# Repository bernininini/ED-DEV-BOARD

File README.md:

# ED-DEV-BOARD
The Ed Dev Board is a custom dev board featuring a Qwiic port and powered by the ESP32-S3 WROOM 1. A custom PCB to provide an easy access and accessible dev board for prototyping and electronics projects that minimize the wiring.

*Qwiic is a type of connecting system that uses the I2C protocol, that only uses 4 pins (VCC, GND, SDA, SCL)

Reference: 
https://www.sparkfun.com/qwiic 

BOM:
| Reference                      | Qty | Value            | Part Name                     |
| ------------------------------ | --- | ---------------- | ----------------------------- |
| QWIIC1, QWIIC2, QWIIC3, QWIIC4 | 4   | port1            | Qwiic Port                    |
| R1, R2                         | 2   | 5.1k             | Resistor 0805                 |
| R3, R4, R5, R6                 | 4   | 10k              | Resistor 0805                 |
| SW1, SW2                       | 2   | SW\_Push         | Push Button 6mm               |
| U1                             | 1   | ESP32-S3-WROOM-1 | ESP32-S3-WROOM-1 Module       |
| U2                             | 1   | AMS1117-3.3      | Voltage Regulator AMS1117-3.3 |
| U3                             | 1   | \~               | USB-C Connector               |

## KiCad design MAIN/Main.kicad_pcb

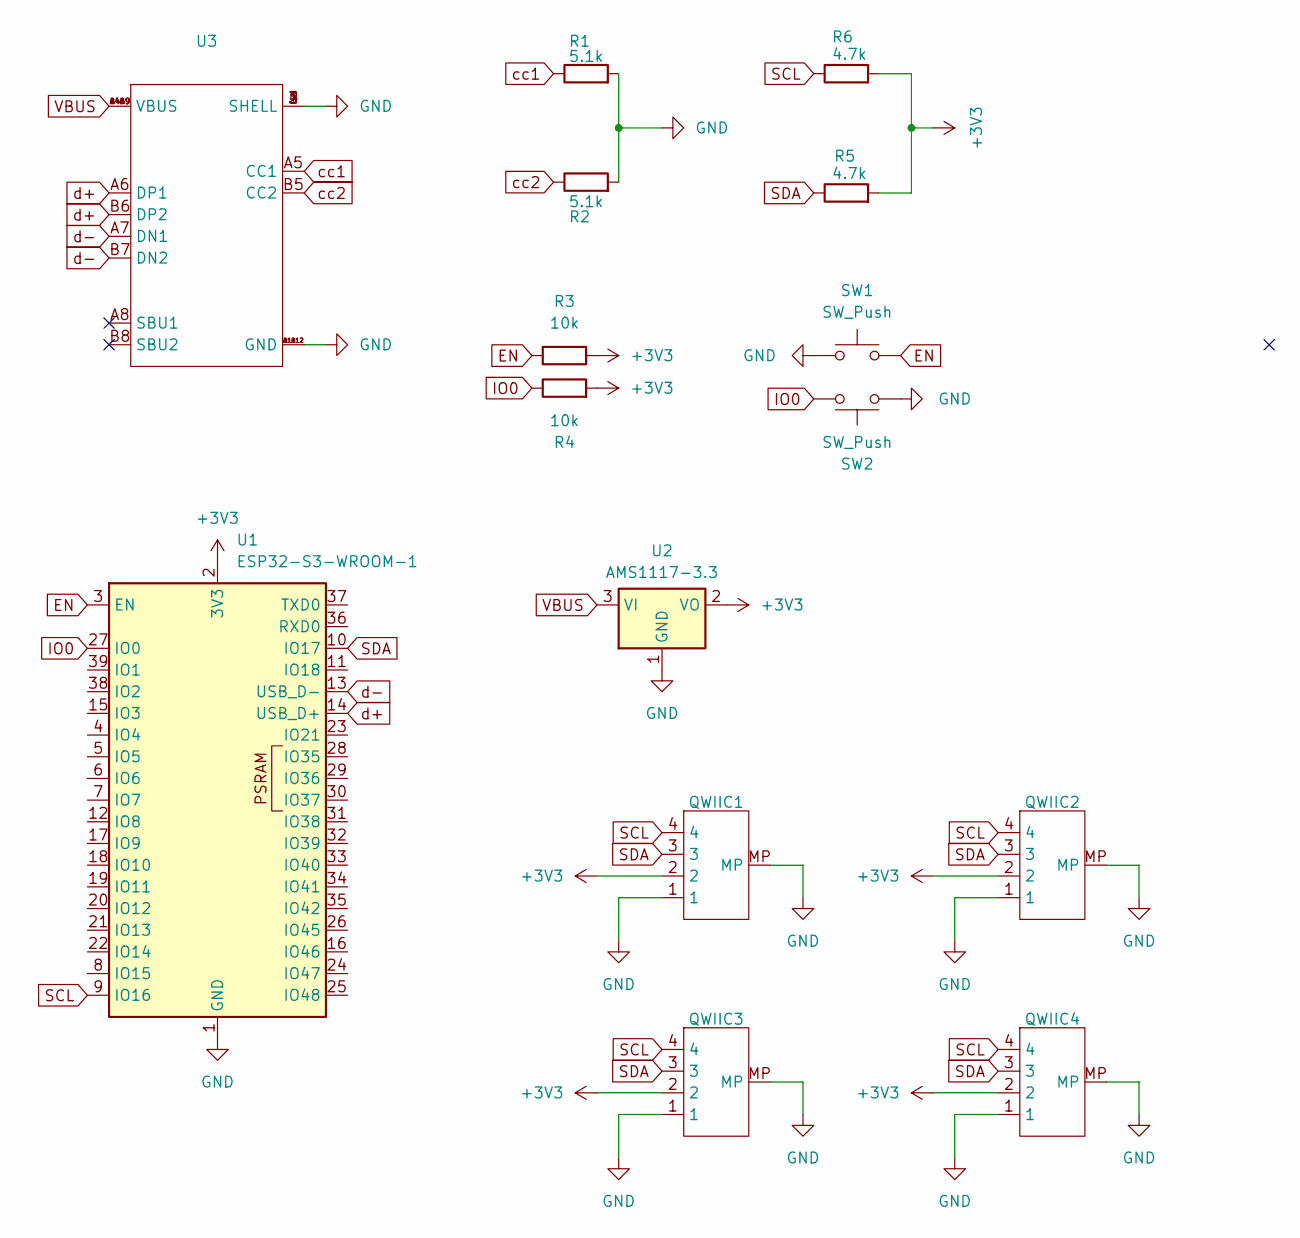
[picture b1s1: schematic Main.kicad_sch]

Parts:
QWIIC1, QWIIC2, QWIIC3, QWIIC4: JST_SH_SM04B-SRSS-TB_1x04-1MP_P1.00mm_Horizontal
R1, R2: 5.1k; R_0805_2012Metric
R3, R4: 10k; R_0805_2012Metric
R5, R6: 4.7k; R_0805_2012Metric
SW1, SW2: SW_Push; SW_PUSH_6mm
U1: ESP32-S3-WROOM-1
U2: AMS1117-3.3; SOT-223-3_TabPin2
U3: USB-C-SMD_G-SWITCH_GT-USB-7010ASV; Manufacturer Part GT-USB-7010ASV; LCSC Part Name Type-C 母 卧贴

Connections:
+3V3: QWIIC1.2, QWIIC2.2, QWIIC3.2, QWIIC4.2, R3.1, R4.2, R5.2, R6.2, U1.2 (3V3), U2.2 (VO)
EN: R3.2, SW1.2, U1.3 (EN)
GND: QWIIC1.1, QWIIC1.MP, QWIIC2.1, QWIIC2.MP, QWIIC3.1, QWIIC3.MP, QWIIC4.1, QWIIC4.MP, R1.2, R2.2, SW1.1, SW2.1, U1.1 (GND), U1.40 (GND), U1.41 (GND), U2.1 (GND), U3.1 (SHELL), U3.2 (SHELL), U3.3 (SHELL), U3.4 (SHELL), U3.A1B12 (GND), U3.B1A12 (GND)
IO0: R4.1, SW2.2, U1.27 (IO0)
SCL: QWIIC1.4, QWIIC2.4, QWIIC3.4, QWIIC4.4, R6.1, U1.9 (IO16)
SDA: QWIIC1.3, QWIIC2.3, QWIIC3.3, QWIIC4.3, R5.1, U1.10 (IO17)
VBUS: U2.3 (VI), U3.A4B9 (VBUS), U3.B4A9 (VBUS)
cc1: R1.1, U3.A5 (CC1)
cc2: R2.1, U3.B5 (CC2)
d+: U1.14 (USB_D+), U3.A6 (DP1), U3.B6 (DP2)
d-: U1.13 (USB_D-), U3.A7 (DN1), U3.B7 (DN2)

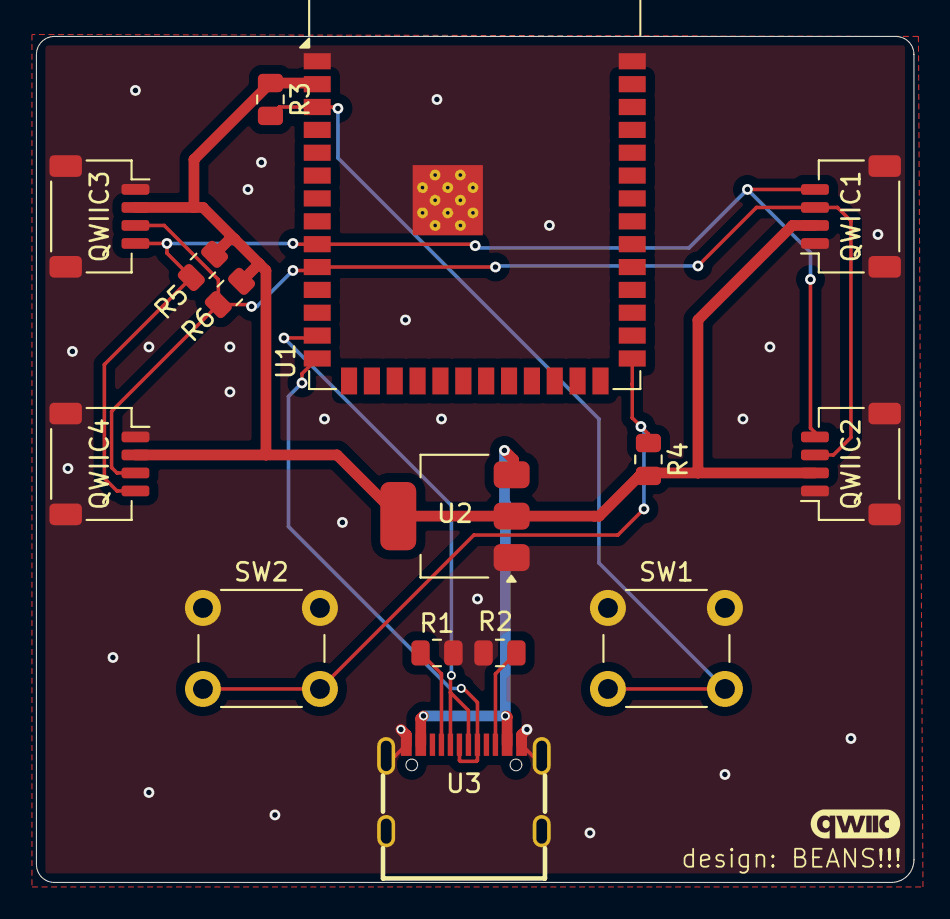
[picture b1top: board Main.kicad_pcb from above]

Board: 2 copper layers, 48.8 x 47.0 mm, 15 parts (0 on the bottom side), 11 nets.

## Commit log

2025-08-18 QWIIC(14417)
2025-08-18 Rename Main.kicad_prl to MAIN/Main.kicad_prl
2025-08-18 Rename Main.kicad_pro to MAIN/Main.kicad_pro
2025-08-18 Rename how-to-import.htm to MAIN/how-to-import.htm
2025-08-18 Rename PRT-14417.kicad_sym to MAIN/PRT-14417.kicad_sym
2025-08-18 Rename SPARKFUN_PRT-14417.kicad_mod to MAIN/SPARKFUN_PRT-14417.kicad_mod
2025-08-18 Rename fp-info-cache to MAIN/fp-info-cache
2025-08-18 Rename MAIN/PRT-14417.kicad_sym to MAIN/QWIIC/PRT-14417.kicad_sym
2025-08-18 Rename MAIN/SPARKFUN_PRT-14417.kicad_mod to MAIN/QWIIC/SPARKFUN_PRT-14417.kicad_mod
2025-08-18 Rename MAIN/how-to-import.htm to MAIN/QWIIC/how-to-import.htm
